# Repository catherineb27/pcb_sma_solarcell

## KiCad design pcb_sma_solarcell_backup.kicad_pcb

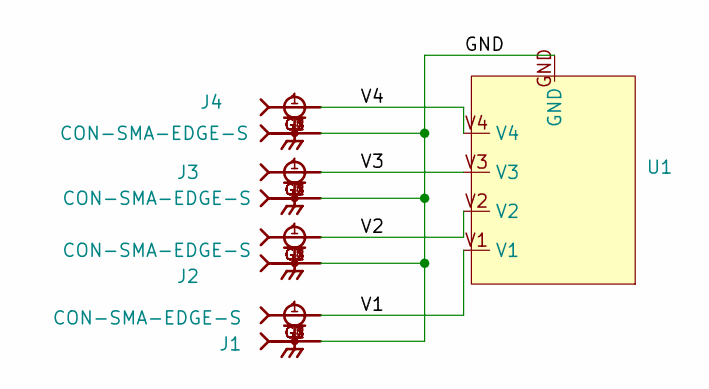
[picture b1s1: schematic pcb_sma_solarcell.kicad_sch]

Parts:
J1, J2, J3, J4: CON-SMA-EDGE-S; RFSOLUTIONS_CON-SMA-EDGE-S; PARTREV 1
U1: sma_topandbot

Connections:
/GND: J1.G1, J1.G2, J1.G3, J1.G4, J2.G1, J2.G2, J2.G3, J2.G4, J3.G1, J3.G2, J3.G3, J3.G4, J4.G1, J4.G2, J4.G3, J4.G4, U1.GND
/V1: J1.1, U1.V1
/V2: J2.1, U1.V2
/V3: J3.1, U1.V3
/V4: J4.1, U1.V4

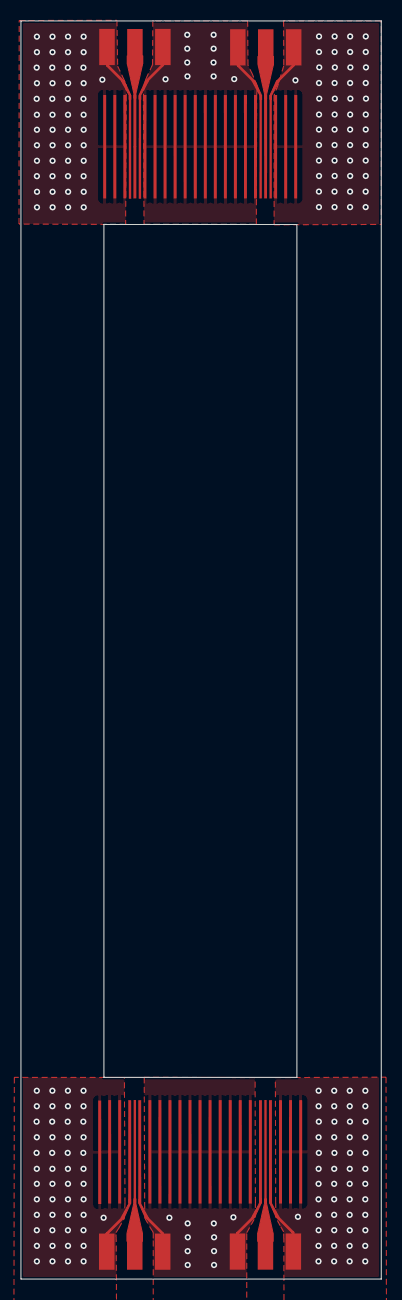
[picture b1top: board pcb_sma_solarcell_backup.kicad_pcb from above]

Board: 2 copper layers, 34.8 x 121.7 mm, 5 parts (0 on the bottom side), 5 nets.

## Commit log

2026-02-09 Describe what changed
